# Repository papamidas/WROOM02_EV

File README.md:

# WROOM02_EV
Micropower IOT Evaluation Board: ESP8266, BME680, BME280, LM75, DS18B20 and TPL5110 nanopower timer for true low power battery operation

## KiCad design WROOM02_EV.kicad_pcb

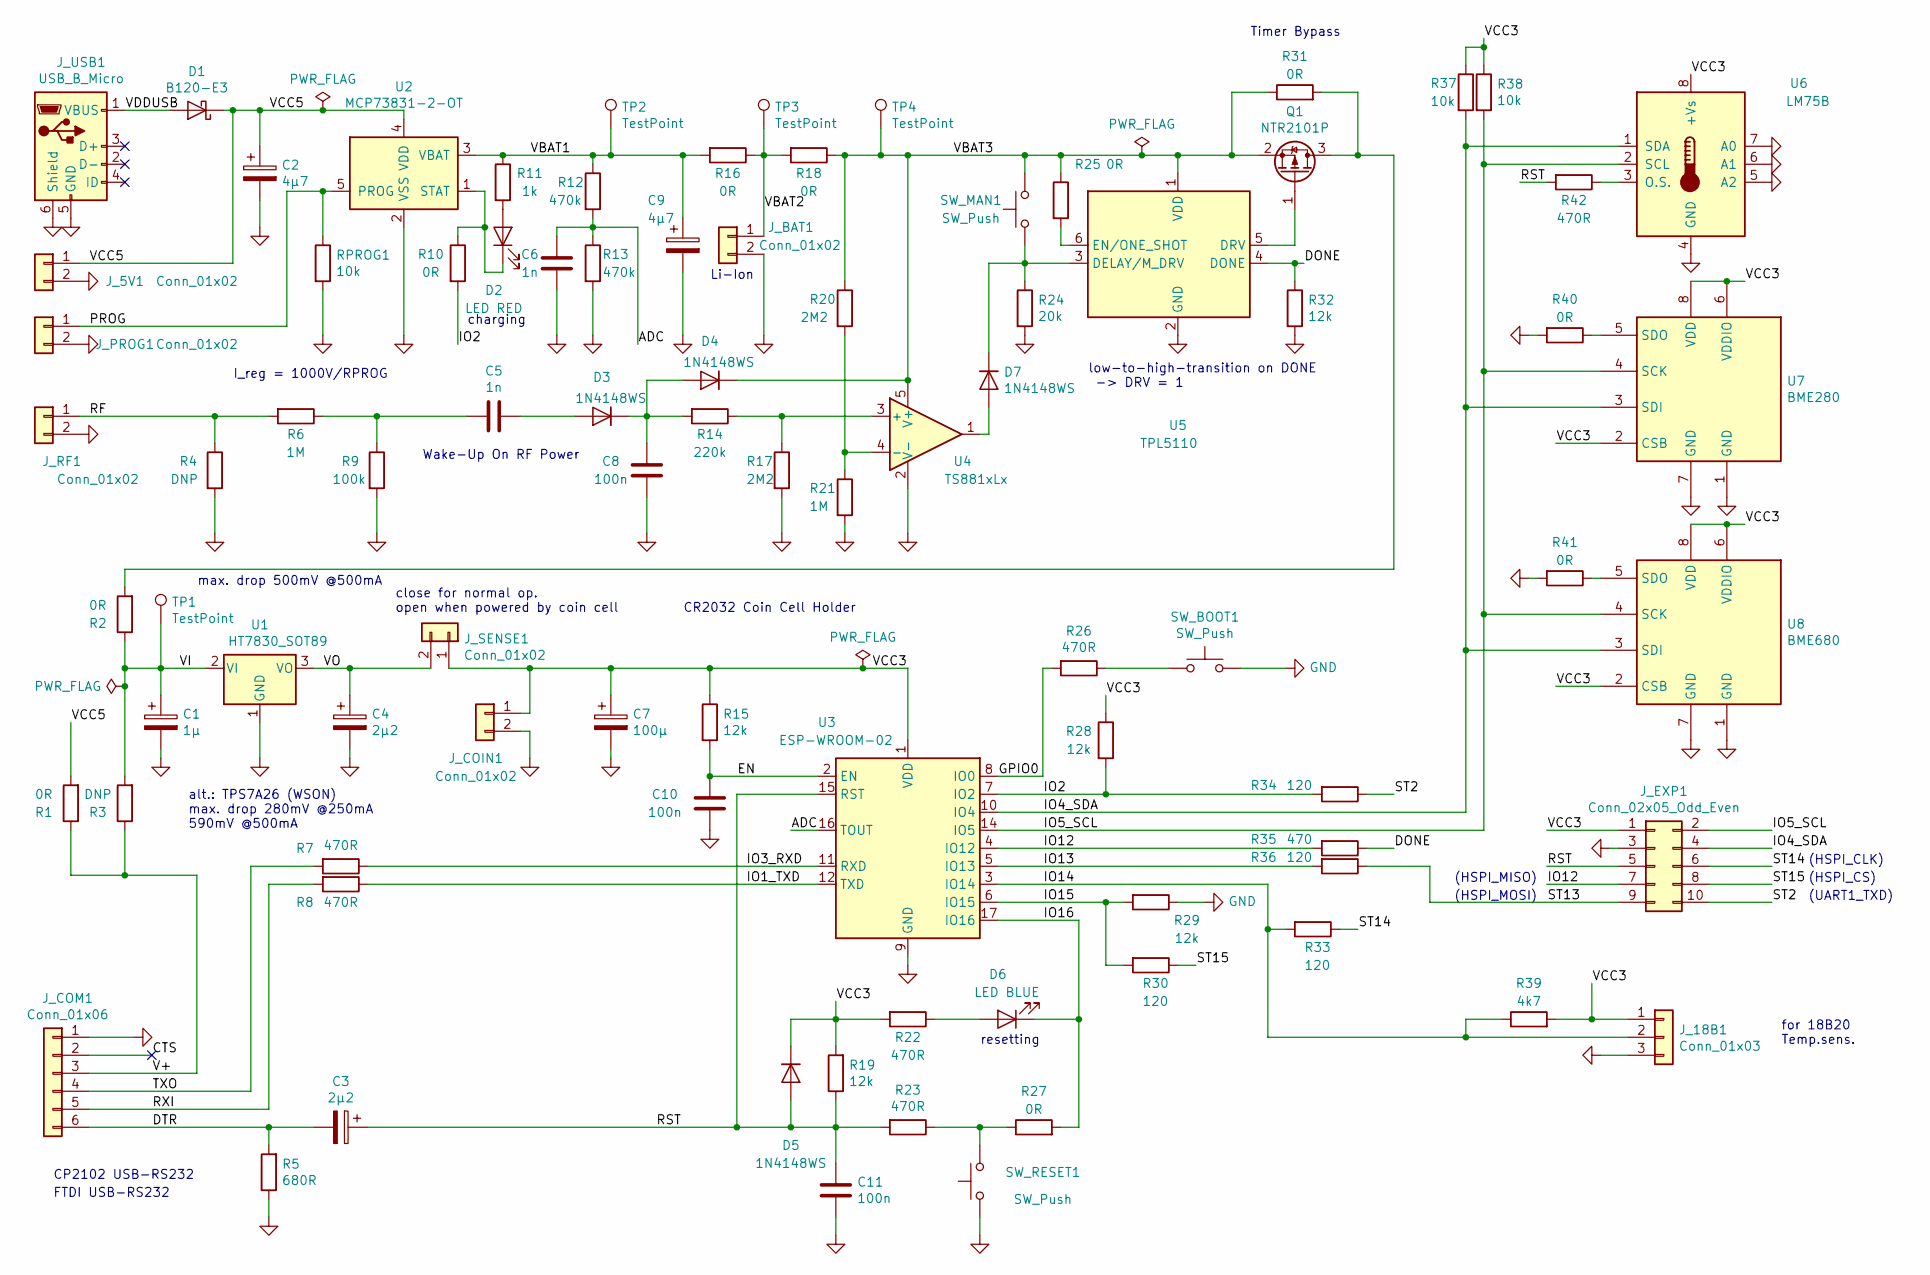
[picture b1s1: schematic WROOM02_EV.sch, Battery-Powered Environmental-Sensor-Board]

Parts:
C1: 1µ; CP_EIA-3528-21_Kemet-B_Pad1.50x2.35mm_HandSolder
C2, C9: 4µ7; CP_EIA-3528-21_Kemet-B_Pad1.50x2.35mm_HandSolder
C3, C4: 2µ2; CP_EIA-3528-21_Kemet-B_Pad1.50x2.35mm_HandSolder
C5, C6: 1n; C_0805_2012Metric_Pad1.15x1.40mm_HandSolder
C7: 100µ; CP_EIA-3528-21_Kemet-B_Pad1.50x2.35mm_HandSolder
C8, C10, C11: 100n; C_0805_2012Metric_Pad1.15x1.40mm_HandSolder
D1: B120-E3; D_SMA
D2: LED RED; LED_0805_2012Metric_Pad1.15x1.40mm_HandSolder
D3, D4, D5, D7: 1N4148WS; D_SOD-323
D6: LED BLUE; LED_0805_2012Metric_Pad1.15x1.40mm_HandSolder
J_5V1: Conn_01x02; PinHeader_1x02_P2.54mm_Vertical
J_18B1: Conn_01x03; PinHeader_1x03_P2.54mm_Vertical
J_BAT1: Conn_01x02; JST_PH_B2B-PH-K_1x02_P2.00mm_Vertical
J_COIN1: Conn_01x02; BatteryHolder_Keystone_1058_1x2032
J_COM1: Conn_01x06; PinHeader_1x06_P2.54mm_Vertical
J_EXP1: Conn_02x05_Odd_Even; PinHeader_2x05_P2.54mm_Vertical
J_PROG1: Conn_01x02; PinHeader_1x02_P2.54mm_Vertical
J_RF1: Conn_01x02; PinHeader_1x02_P2.54mm_Vertical
J_SENSE1: Conn_01x02; PinHeader_1x02_P2.54mm_Vertical
J_USB1: USB_B_Micro; USB_Micro-B_Wuerth_629105150521
Q1: NTR2101P; SOT-23
R1, R2, R10, R16, R18, R25, R27, R31, R40, R41: 0R; R_0805_2012Metric_Pad1.15x1.40mm_HandSolder
R3, R4: DNP; R_0805_2012Metric_Pad1.15x1.40mm_HandSolder
R5: 680R; R_0805_2012Metric_Pad1.15x1.40mm_HandSolder
R6, R21: 1M; R_0805_2012Metric_Pad1.15x1.40mm_HandSolder
R7, R8, R22, R23, R26, R42: 470R; R_0805_2012Metric_Pad1.15x1.40mm_HandSolder
R9: 100k; R_0805_2012Metric_Pad1.15x1.40mm_HandSolder
R11: 1k; R_0805_2012Metric_Pad1.15x1.40mm_HandSolder
R12, R13: 470k; R_0805_2012Metric_Pad1.15x1.40mm_HandSolder
R14: 220k; R_0805_2012Metric_Pad1.15x1.40mm_HandSolder
R15, R19, R28, R29, R32: 12k; R_0805_2012Metric_Pad1.15x1.40mm_HandSolder
R17, R20: 2M2; R_0805_2012Metric_Pad1.15x1.40mm_HandSolder
R24: 20k; R_0805_2012Metric_Pad1.15x1.40mm_HandSolder
R30, R33, R34, R36: 120; R_0805_2012Metric_Pad1.15x1.40mm_HandSolder
R35: 470; R_0805_2012Metric_Pad1.15x1.40mm_HandSolder
R37, R38: 10k; R_0805_2012Metric_Pad1.15x1.40mm_HandSolder
R39: 4k7; R_0805_2012Metric_Pad1.15x1.40mm_HandSolder
RPROG1: 10k; R_0805_2012Metric_Pad1.15x1.40mm_HandSolder
SW_BOOT1: SW_Push; SW_Push_SPST_NO_Alps_SKRK
SW_MAN1: SW_Push; SW_Push_SPST_NO_Alps_SKRK
SW_RESET1: SW_Push; SW_Push_SPST_NO_Alps_SKRK
TP1, TP2, TP3, TP4: TestPoint; TestPoint_Keystone_5000-5004_Miniature
U1: HT7830_SOT89; SOT-89-3
U2: MCP73831-2-OT; SOT-23-5
U3: ESP-WROOM-02
U4: TS881xLx; SOT-23-5
U5: TPL5110; SOT-23-6
U6: LM75B; TSSOP-8_3x3mm_P0.65mm
U7: BME280; Bosch_LGA-8_2.5x2.5mm_P0.65mm_ClockwisePinNumbering
U8: BME680; Bosch_LGA-8_3x3mm_P0.8mm_ClockwisePinNumbering

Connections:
/ADC: C6.1, R12.2, R13.1, U3.16 (TOUT)
/CTS: J_COM1.2
/DONE: R32.1, R35.1, U5.4 (DONE)
/DTR: C3.2, J_COM1.6, R5.2
/EN: C10.1, R15.2, U3.2 (EN)
/GPIO0: R26.2, U3.8 (IO0)
/IO1_TXD: R8.1, U3.12 (TXD)
/IO2: R10.2, R28.2, R34.2, U3.7 (IO2)
/IO3_RXD: R7.1, U3.11 (RXD)
/IO4_SDA: J_EXP1.4, R37.2, U3.10 (IO4), U6.1 (SDA), U7.3 (SDI), U8.3 (SDI)
/IO5_SCL: J_EXP1.2, R38.2, U3.14 (IO5), U6.2 (SCL), U7.4 (SCK), U8.4 (SCK)
/IO12: J_EXP1.7, R35.2, U3.4 (IO12)
/IO13: R36.2, U3.5 (IO13)
/IO14: J_18B1.2, R33.2, R39.1, U3.3 (IO14)
/IO15: R29.2, R30.2, U3.6 (IO15)
/IO16: D6.1 (K), R27.2, U3.17 (IO16)
/PROG: J_PROG1.1, RPROG1.1, U2.5 (PROG)
/RF: J_RF1.1, R4.1, R6.2
/RST: C3.1, C11.2, D5.2 (A), J_EXP1.5, R19.1, R23.2, R42.2, U3.15 (RST)
/RXI: J_COM1.5, R8.2
/ST2: J_EXP1.10, R34.1
/ST13: J_EXP1.9, R36.1
/ST14: J_EXP1.6, R33.1
/ST15: J_EXP1.8, R30.1
/TXO: J_COM1.4, R7.2
/V+: J_COM1.3, R1.1, R3.1
/VBAT1: C9.1, R11.1, R12.1, R16.2, TP2.1, U2.3 (VBAT)
/VBAT2: J_BAT1.1, R16.1, R18.2, TP3.1
/VBAT3: D4.1 (K), Q1.2 (S), R18.1, R20.1, R25.1, R31.1, SW_MAN1.1, TP4.1, U4.5 (V+), U5.1 (VDD)
/VCC3: C7.1, D5.1 (K), J_18B1.1, J_COIN1.1, J_EXP1.1, J_SENSE1.1, R15.1, R19.2, R22.2, R28.1, R37.1, R38.1, R39.2, U3.1 (VDD), U6.8 (+Vs), U7.2 (CSB), U7.6 (VDDIO), U7.8 (VDD), U8.2 (CSB), U8.6 (VDDIO), U8.8 (VDD)
/VCC5: C2.1, D1.1 (K), J_5V1.1, R1.2, U2.4 (VDD)
/VDDUSB: D1.2 (A), J_USB1.1 (VBUS)
/VI: C1.1, R2.1, R3.2, TP1.1, U1.2 (VI)
/VO: C4.1, J_SENSE1.2, U1.3 (VO)
GND: C1.2, C2.2, C4.2, C6.2, C7.2, C8.2, C9.2, C10.2, C11.1, J_5V1.2, J_18B1.3, J_BAT1.2, J_COIN1.2, J_COM1.1, J_EXP1.3, J_PROG1.2, J_RF1.2, J_USB1.5 (GND), J_USB1.6 (Shield), R4.2, R5.1, R9.2, R13.2, R17.2, R21.2, R24.2, R29.1, R32.2, R40.2, R41.2, RPROG1.2, SW_BOOT1.2, SW_RESET1.1, U1.1 (GND), U2.2 (VSS), U3.9 (GND), U3.13 (GND), U3.18 (GND), U3.19 (GND), U4.2 (V-), U5.2 (GND), U6.4 (GND), U6.5 (A2), U6.6 (A1), U6.7 (A0), U7.1 (GND), U7.7 (GND), U8.1 (GND), U8.7 (GND)
unnamed: C5.1, D3.2 (A)
unnamed: C5.2, R6.1, R9.1
unnamed: C8.1, D3.1 (K), D4.2 (A), R14.2
unnamed: D2.1 (K), R10.1, U2.1 (STAT)
unnamed: D2.2 (A), R11.2
unnamed: D6.2 (A), R22.1
unnamed: D7.1 (K), R24.1, SW_MAN1.2, U5.3 (DELAY/M_DRV)
unnamed: D7.2 (A), U4.1
unnamed: Q1.1 (G), U5.5 (DRV)
unnamed: Q1.3 (D), R2.2, R31.2
unnamed: R14.1, R17.1, U4.3 (+)
unnamed: R20.2, R21.1, U4.4 (-)
unnamed: R23.1, R27.1, SW_RESET1.2
unnamed: R25.2, U5.6 (EN/ONE_SHOT)
unnamed: R26.1, SW_BOOT1.1
unnamed: R40.1, U7.5 (SDO)
unnamed: R41.1, U8.5 (SDO)
unnamed: R42.1, U6.3 (O.S.)

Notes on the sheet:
FTDI USB-RS232
CP2102 USB-RS232
CR2032 Coin Cell Holder
Li-Ion
close for normal op. open when powered by coin cell
Timer Bypass
for 18B20 Temp.sens.
low-to-high-transition on DONE -> DRV = 1
Wake-Up On RF Power
(HSPI_MISO)
(HSPI_MOSI)
(HSPI_CS)
(UART1_TXD)
I_reg = 1000V/RPROG
(HSPI_CLK)
alt.: TPS7A26 (WSON) max. drop 280mV @250mA 590mV @500mA
max. drop 500mV @500mA
charging
resetting

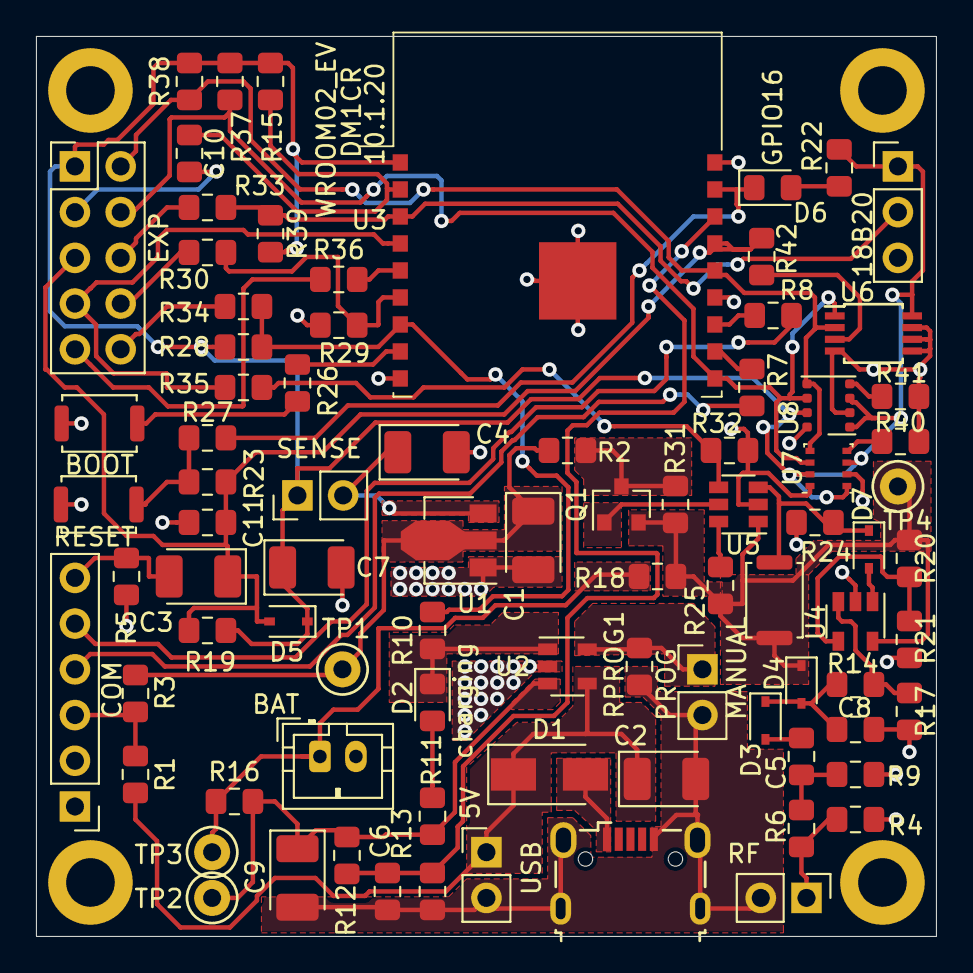
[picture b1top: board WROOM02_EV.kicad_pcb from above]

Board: 2 copper layers, 50.0 x 50.0 mm, 87 parts (1 on the bottom side), 52 nets.

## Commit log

2020-01-11 First version, uploaded to JLC
2020-01-11 schematic pdf output added
2020-01-11 3d view of board added
